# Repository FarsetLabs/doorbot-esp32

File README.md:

# doorbot-esp32

RFID Card Reader and Door Relay Opening Module for use with the [doorbot](https://www.github.com/FarsetLabs/doorbot) project.

It's general operation is:

* Setup Wi-Fi Connection*
* Setup MFRC522 Card Connection
* Loop waiting for card presence detection
* On Card Detect, Grab the UID from the presented Card
* Attempt to trigger an 'open' action* on the door identified by the onboard device_id, using the same device id and the UID from the presented card as the Username and Password for HTTP Basic Auth
* If 200 response; flash green on RGB LED and unlock door via relay for 5 seconds
* Otherwise flash red for 5 seconds and resume loop

*Configured through build-time environment variables, see `platform.ini` for details

## Hardware Setup

This project uses an ESP-WROOM-32 package, an RC522 RFID module

### Pin Mappings:

#### RC522 -> ESP32

| RC522 | ESP32   | Description       |
| ----- | ------- | ----------------- |
| 3v3   | 3v3     | VIN               |
| RST   | D22     | Reset             |
| GND   | GND     | Ground            |
| IRQ   | <Blank> | Unused            |
| MISO  | D19     | SPI Master Input  |
| MOSI  | D23     | SPI Master Output |
| SCK   | D18     | SPI Clock         |
| SDA   | D21     | Serial Data Line  |

#### RGB LED -> ESP32

| RGB LED | ESP32   | Description |
| ------- | ------- | ----------- |
| (-)     | GND     | Ground      |
| R       | D2      | Red         |
| G       | D4      | Green       |
| B       | <blank> | Blue        |

#### RELAY -> ESP32

| RELAY | ESP32 |                          |
| ----- | ----- | ------------------------ |
| NO    | D15   | Normally Open (Actuator) |
| +     | 3v3   | +VE                      |
| -     | GND   | Ground                   |

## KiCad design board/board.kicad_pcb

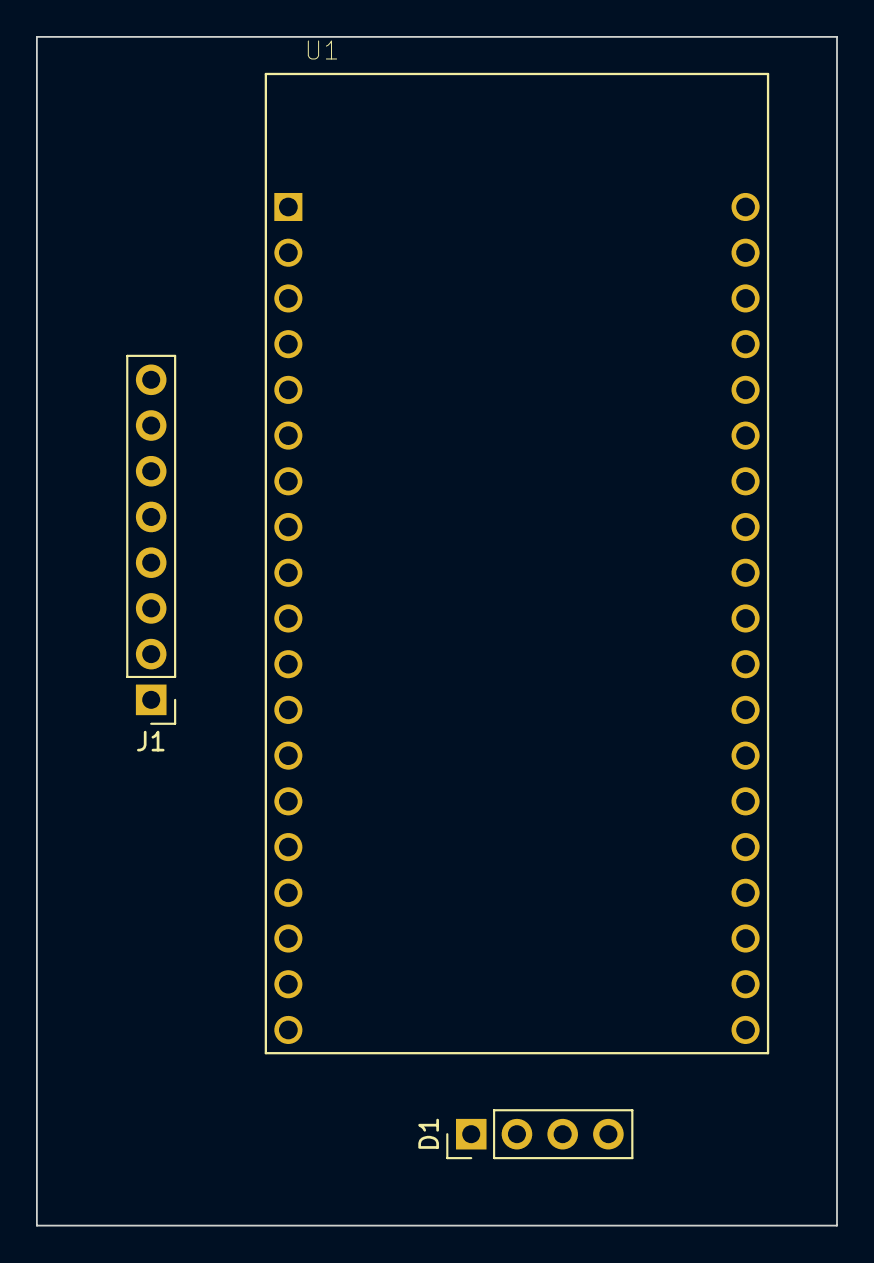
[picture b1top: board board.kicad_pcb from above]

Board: 2 copper layers, 44.4 x 66.0 mm, 3 parts (0 on the bottom side), 10 nets, no tracks yet.

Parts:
D1: LED_ARBG; PinHeader_1x04_P2.54mm_Vertical
J1: RFID-RC522; PinHeader_1x08_P2.54mm_Vertical
U1: ESP32-DEVKITC-32D; MODULE_ESP32-DEVKITC-32D

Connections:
unnamed: D1.1, J1.6, U1.2
unnamed: D1.2, U1.5
unnamed: D1.3, U1.4
unnamed: D1.4, U1.3
unnamed: J1.1, U1.15
unnamed: J1.2, U1.13
unnamed: J1.3, U1.19
unnamed: J1.4, U1.14
unnamed: J1.7, U1.18
unnamed: J1.8, U1.1

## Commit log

2020-06-15 That might do it, probably a mess
2020-06-16 Added draft board stuff and more documentation
2021-06-27 Actually working with Nexudus!
2023-04-11 2023 updates; shocked that it kinda sorta works if my electronics were a bit better...
